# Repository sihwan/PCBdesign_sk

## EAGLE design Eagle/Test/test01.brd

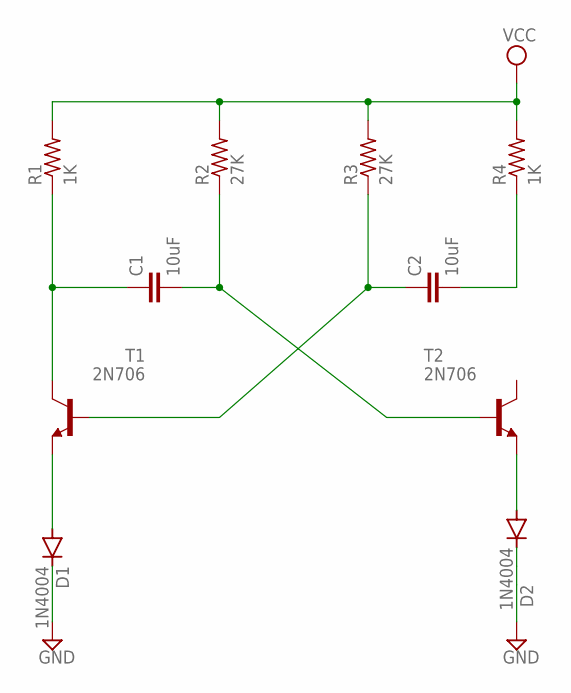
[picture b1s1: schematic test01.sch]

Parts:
C1, C2: 10uF; C2.5-3
D1, D2: 1N4004; DO41-10
R1, R4: 1K; 0204/7
R2, R3: 27K; 0204/7
T1, T2: 2N706; TO18

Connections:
GND: D1.C, D2.C
unnamed: D1.A, T1.1 (E)
unnamed: C1.1, R1.1, T1.3 (C)
unnamed: C1.2, R2.1, T2.2 (B)
unnamed: C2.1, R3.1, T1.2 (B)
unnamed: C2.2, R4.1
unnamed: D2.A, T2.1 (E)
VCC: R1.2, R2.2, R3.2, R4.2

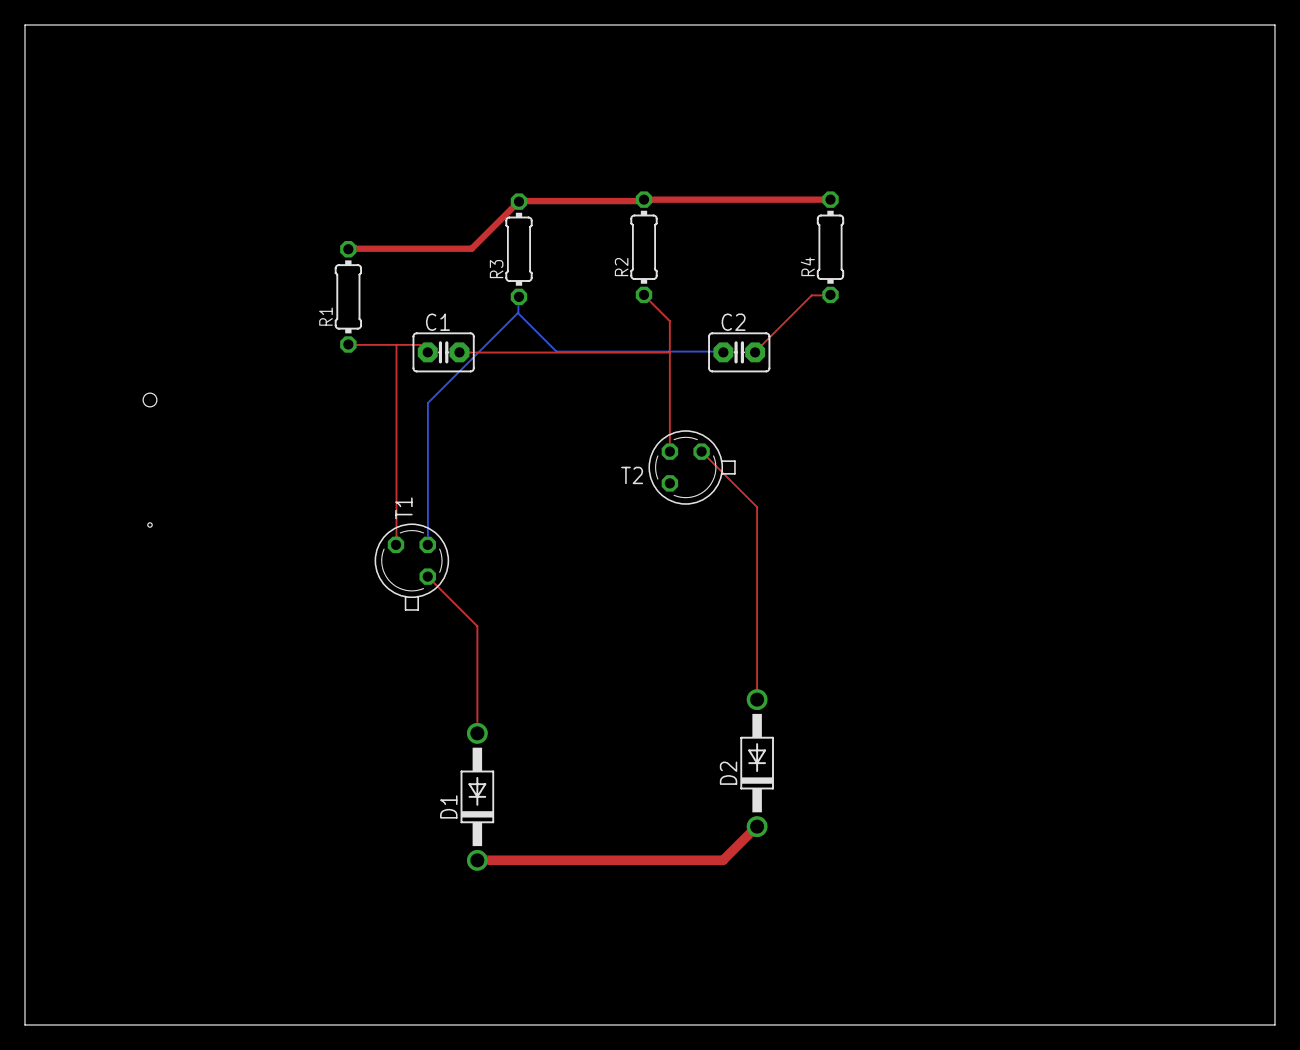
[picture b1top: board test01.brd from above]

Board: 2 copper layers, 100.0 x 80.0 mm, 10 parts (0 on the bottom side), 8 nets.

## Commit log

2018-05-18 initial_commit
2018-05-22 Test
    Test
2018-07-08 f5529 pdf
    add
2018-07-10 a
    a
2018-07-10 BOM
    BOM, excel sheet
2018-07-10 info
    info
2018-07-10 update
    update
2018-08-09 yb
    080818
2018-08-09 YB
    YB
